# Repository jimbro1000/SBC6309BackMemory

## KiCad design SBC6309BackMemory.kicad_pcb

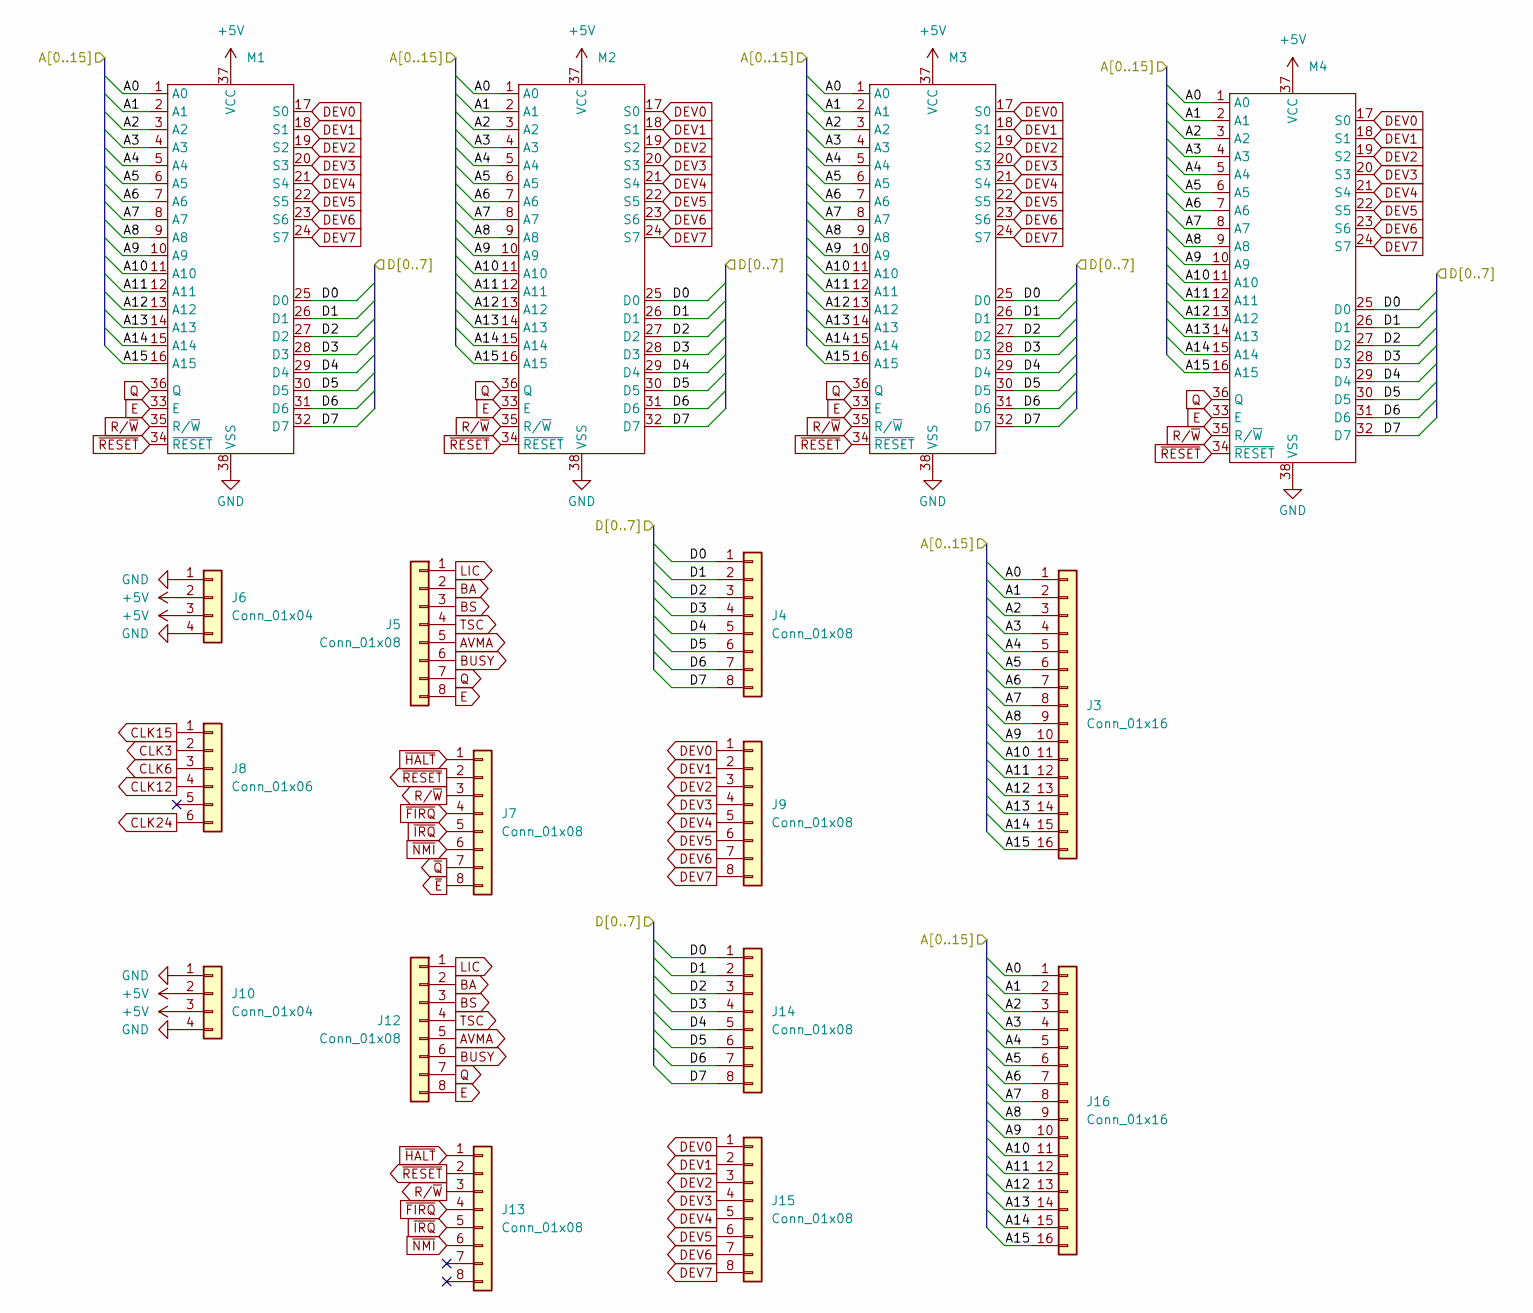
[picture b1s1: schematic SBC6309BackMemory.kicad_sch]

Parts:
J3, J16: Conn_01x16; PinHeader_1x16_P2.54mm_Vertical
J4, J5, J7, J9, J12, J13, J14, J15: Conn_01x08; PinHeader_1x08_P2.54mm_Vertical
J6, J10: Conn_01x04; PinHeader_1x04_P2.54mm_Vertical
J8: Conn_01x06; PinHeader_1x06_P2.54mm_Vertical
M1, M2, M3, M4: Ram

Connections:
+5V: J6.2, J6.3, J10.2, J10.3, M1.37 (VCC), M2.37 (VCC), M3.37 (VCC), M4.37 (VCC)
/A0: J3.1, J16.1, M1.1 (A0), M2.1 (A0), M3.1 (A0), M4.1 (A0)
/A1: J3.2, J16.2, M1.2 (A1), M2.2 (A1), M3.2 (A1), M4.2 (A1)
/A2: J3.3, J16.3, M1.3 (A2), M2.3 (A2), M3.3 (A2), M4.3 (A2)
/A3: J3.4, J16.4, M1.4 (A3), M2.4 (A3), M3.4 (A3), M4.4 (A3)
/A4: J3.5, J16.5, M1.5 (A4), M2.5 (A4), M3.5 (A4), M4.5 (A4)
/A5: J3.6, J16.6, M1.6 (A5), M2.6 (A5), M3.6 (A5), M4.6 (A5)
/A6: J3.7, J16.7, M1.7 (A6), M2.7 (A6), M3.7 (A6), M4.7 (A6)
/A7: J3.8, J16.8, M1.8 (A7), M2.8 (A7), M3.8 (A7), M4.8 (A7)
/A8: J3.9, J16.9, M1.9 (A8), M2.9 (A8), M3.9 (A8), M4.9 (A8)
/A9: J3.10, J16.10, M1.10 (A9), M2.10 (A9), M3.10 (A9), M4.10 (A9)
/A10: J3.11, J16.11, M1.11 (A10), M2.11 (A10), M3.11 (A10), M4.11 (A10)
/A11: J3.12, J16.12, M1.12 (A11), M2.12 (A11), M3.12 (A11), M4.12 (A11)
/A12: J3.13, J16.13, M1.13 (A12), M2.13 (A12), M3.13 (A12), M4.13 (A12)
/A13: J3.14, J16.14, M1.14 (A13), M2.14 (A13), M3.14 (A13), M4.14 (A13)
/A14: J3.15, J16.15, M1.15 (A14), M2.15 (A14), M3.15 (A14), M4.15 (A14)
/A15: J3.16, J16.16, M1.16 (A15), M2.16 (A15), M3.16 (A15), M4.16 (A15)
/D0: J4.1, J14.1, M1.25 (D0), M2.25 (D0), M3.25 (D0), M4.25 (D0)
/D1: J4.2, J14.2, M1.26 (D1), M2.26 (D1), M3.26 (D1), M4.26 (D1)
/D2: J4.3, J14.3, M1.27 (D2), M2.27 (D2), M3.27 (D2), M4.27 (D2)
/D3: J4.4, J14.4, M1.28 (D3), M2.28 (D3), M3.28 (D3), M4.28 (D3)
/D4: J4.5, J14.5, M1.29 (D4), M2.29 (D4), M3.29 (D4), M4.29 (D4)
/D5: J4.6, J14.6, M1.30 (D5), M2.30 (D5), M3.30 (D5), M4.30 (D5)
/D6: J4.7, J14.7, M1.31 (D6), M2.31 (D6), M3.31 (D6), M4.31 (D6)
/D7: J4.8, J14.8, M1.32 (D7), M2.32 (D7), M3.32 (D7), M4.32 (D7)
AVMA: J5.5, J12.5
BA: J5.2, J12.2
BS: J5.3, J12.3
BUSY: J5.6, J12.6
CLK3: J8.2
CLK6: J8.3
CLK12: J8.4
CLK15: J8.1
CLK24: J8.6
DEV0: J9.1, J15.1, M1.17 (S0), M2.17 (S0), M3.17 (S0), M4.17 (S0)
DEV1: J9.2, J15.2, M1.18 (S1), M2.18 (S1), M3.18 (S1), M4.18 (S1)
DEV2: J9.3, J15.3, M1.19 (S2), M2.19 (S2), M3.19 (S2), M4.19 (S2)
DEV3: J9.4, J15.4, M1.20 (S3), M2.20 (S3), M3.20 (S3), M4.20 (S3)
DEV4: J9.5, J15.5, M1.21 (S4), M2.21 (S4), M3.21 (S4), M4.21 (S4)
DEV5: J9.6, J15.6, M1.22 (S5), M2.22 (S5), M3.22 (S5), M4.22 (S5)
DEV6: J9.7, J15.7, M1.23 (S6), M2.23 (S6), M3.23 (S6), M4.23 (S6)
DEV7: J9.8, J15.8, M1.24 (S7), M2.24 (S7), M3.24 (S7), M4.24 (S7)
E: J5.8, J12.8, M1.33 (E), M2.33 (E), M3.33 (E), M4.33 (E)
GND: J6.1, J6.4, J10.1, J10.4, M1.38 (VSS), M2.38 (VSS), M3.38 (VSS), M4.38 (VSS)
LIC: J5.1, J12.1
Q: J5.7, J12.7, M1.36 (Q), M2.36 (Q), M3.36 (Q), M4.36 (Q)
R/~W: J7.3, J13.3, M1.35 (R/~W), M2.35 (R/~W), M3.35 (R/~W), M4.35 (R/~W)
TSC: J5.4, J12.4
~E: J7.8
~FIRQ: J7.4, J13.4
~HALT: J7.1, J13.1
~IRQ: J7.5, J13.5
~NMI: J7.6, J13.6
~Q: J7.7
~RESET: J7.2, J13.2, M1.34 (~RESET), M2.34 (~RESET), M3.34 (~RESET), M4.34 (~RESET)

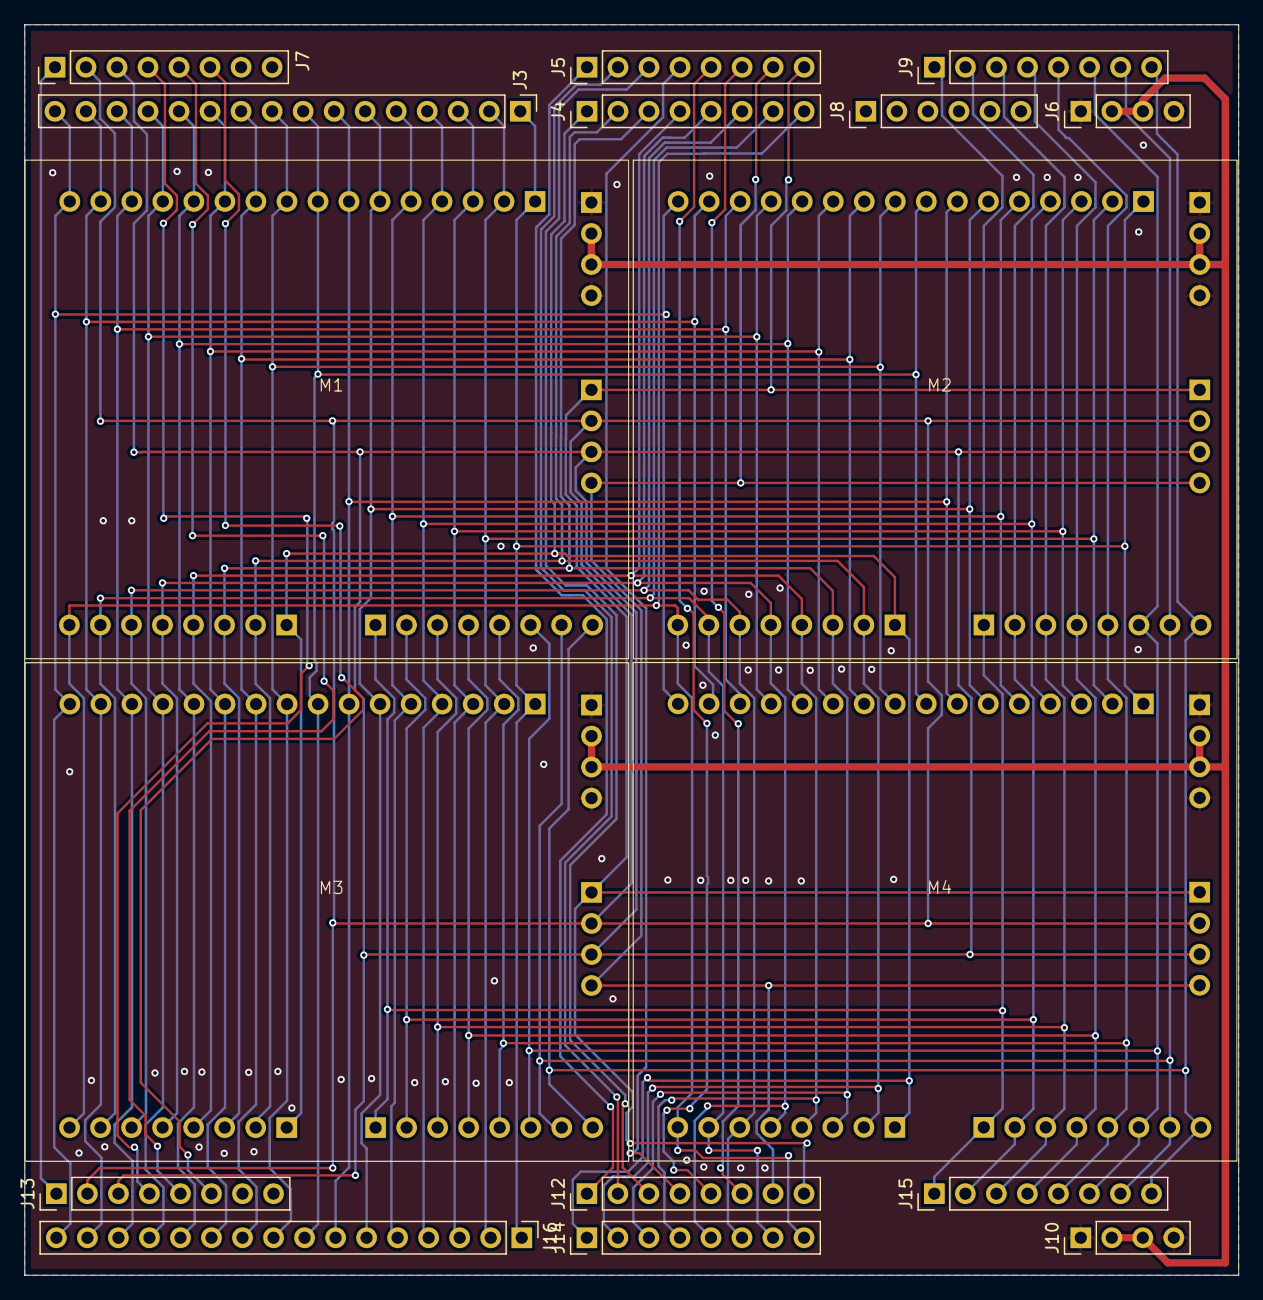
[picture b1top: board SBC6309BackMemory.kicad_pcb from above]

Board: 2 copper layers, 99.4 x 102.4 mm, 17 parts (0 on the bottom side), 48 nets.

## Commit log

2025-05-14 route primary functional traces
2025-05-14 add pass through connections
2025-05-14 finish routing
